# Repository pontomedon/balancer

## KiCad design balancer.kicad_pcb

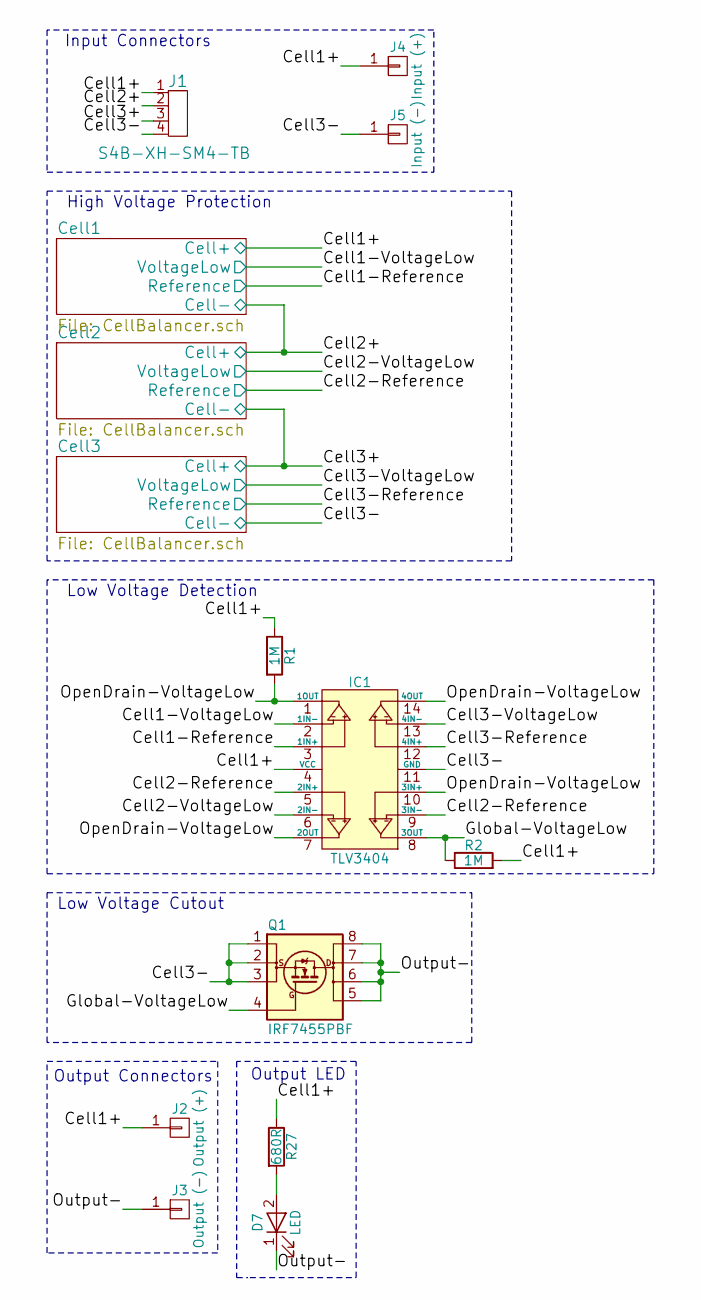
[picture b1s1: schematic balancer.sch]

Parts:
D7: LED; LED_0805
IC1: TLV3404; SOIC-14_3.9x8.7mm_Pitch1.27mm
J1: S4B-XH-SM4-TB; JST_XH_S4B-XH-SM4-TB_04x2.50mm_Angled
J2: Output (+); Solder_Terminal_4x4mm
J3: Output (-); Solder_Terminal_4x4mm
J4: Input (+); Solder_Terminal_4x4mm
J5: Input (-); Solder_Terminal_4x4mm
Q1: IRF7455PBF; SOIC-8_3.9x4.9mm_Pitch1.27mm
R1, R2: 1M; R_0805
R27: 680R; R_0805

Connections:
/Cell1+: IC1.4 (VCC), J1.1, J2.1, J4.1, R1.1, R2.2, R27.1; also elsewhere on the board
/Cell1-Reference: IC1.3 (1IN+); also elsewhere on the board
/Cell1-VoltageLow: IC1.2 (1IN-); also elsewhere on the board
/Cell2+: J1.2; also elsewhere on the board
/Cell2-Reference: IC1.5 (2IN+), IC1.9 (3IN-); also elsewhere on the board
/Cell2-VoltageLow: IC1.6 (2IN-); also elsewhere on the board
/Cell3+: J1.3; also elsewhere on the board
/Cell3-: IC1.11 (GND), J1.4, J5.1, Q1.1 (S), Q1.2 (S), Q1.3 (S); also elsewhere on the board
/Cell3-Reference: IC1.12 (4IN+); also elsewhere on the board
/Cell3-VoltageLow: IC1.13 (4IN-); also elsewhere on the board
/Global-VoltageLow: IC1.8 (3OUT), Q1.4 (G), R2.1
/OpenDrain-VoltageLow: IC1.1 (1OUT), IC1.7 (2OUT), IC1.10 (3IN+), IC1.14 (4OUT), R1.2
/Output-: D7.1 (K), J3.1, Q1.5 (D), Q1.6 (D), Q1.7 (D), Q1.8 (D)
unnamed: D7.2 (A), R27.2

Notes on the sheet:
Input Connectors
High Voltage Protection
Low Voltage Detection
Low Voltage Cutout
Output Connectors
Output LED

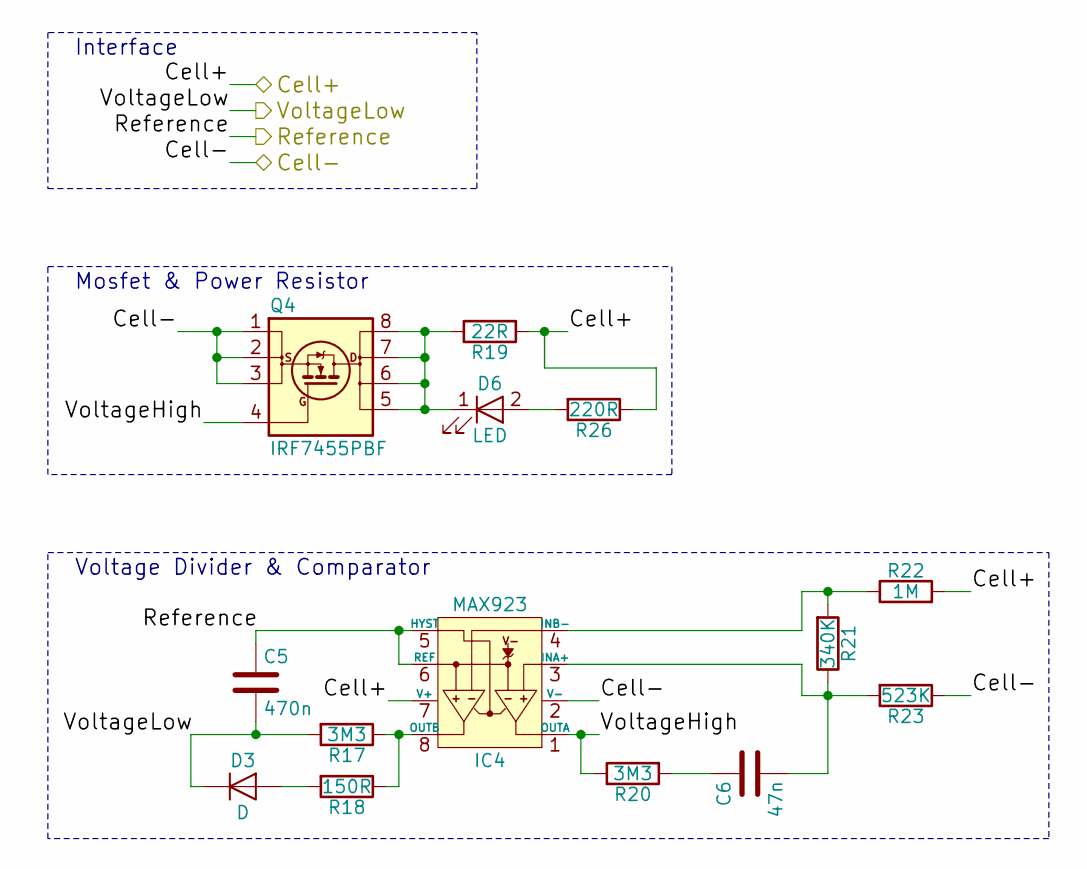
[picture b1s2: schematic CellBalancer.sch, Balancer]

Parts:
C1: 470n; C_0805
C2: 47n; C_0805
D1: D; D_0805
D4: LED; LED_0805
IC2: MAX923; SOIC-8_3.9x4.9mm_Pitch1.27mm
Q2: IRF7455PBF; SOIC-8_3.9x4.9mm_Pitch1.27mm
R3, R6: 3M3; R_0805
R4: 150R; R_0805
R5: 22R; R_0612
R7: 340K; R_0805
R8: 1M; R_0805
R9: 523K; R_0805
R24: 220R; R_0805

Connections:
/Cell1+: IC2.7 (V+), R5.2, R8.2, R24.1; also elsewhere on the board
/Cell1-Reference: C1.1, IC2.5 (HYST), IC2.6 (REF); also elsewhere on the board
/Cell1-VoltageLow: C1.2, D1.1 (K), R3.2; also elsewhere on the board
/Cell1/VoltageHigh: IC2.1 (OUTA), Q2.4 (G), R6.1
/Cell2+: IC2.2 (V-), Q2.1 (S), Q2.2 (S), Q2.3 (S), R9.1; also elsewhere on the board
unnamed: C2.1, R6.2
unnamed: C2.2, IC2.3 (INA+), R7.1, R9.2
unnamed: D1.2 (A), R4.2
unnamed: D4.1 (K), Q2.5 (D), Q2.6 (D), Q2.7 (D), Q2.8 (D), R5.1
unnamed: D4.2 (A), R24.2
unnamed: IC2.4 (INB-), R7.2, R8.1
unnamed: IC2.8 (OUTB), R3.1, R4.1

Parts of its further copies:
C3, C5: 470n; C_0805
C4, C6: 47n; C_0805
D2, D3: D; D_0805
D5, D6: LED; LED_0805
IC3, IC4: MAX923; SOIC-8_3.9x4.9mm_Pitch1.27mm
Q3, Q4: IRF7455PBF; SOIC-8_3.9x4.9mm_Pitch1.27mm
R10, R13, R17, R20: 3M3; R_0805
R11, R18: 150R; R_0805
R12, R19: 22R; R_0612
R14, R21: 340K; R_0805
R15, R22: 1M; R_0805
R16, R23: 523K; R_0805
R25, R26: 220R; R_0805

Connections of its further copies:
/Cell2+: IC3.7 (V+), R12.2, R15.2, R25.1; also elsewhere on the board
/Cell2-Reference: C3.1, IC3.5 (HYST), IC3.6 (REF); also elsewhere on the board
/Cell2-VoltageLow: C3.2, D2.1 (K), R10.2; also elsewhere on the board
/Cell2/VoltageHigh: IC3.1 (OUTA), Q3.4 (G), R13.1
/Cell3+: IC3.2 (V-), IC4.7 (V+), Q3.1 (S), Q3.2 (S), Q3.3 (S), R16.1, R19.2, R22.2, R26.1; also elsewhere on the board
/Cell3-: IC4.2 (V-), Q4.1 (S), Q4.2 (S), Q4.3 (S), R23.1; also elsewhere on the board
/Cell3-Reference: C5.1, IC4.5 (HYST), IC4.6 (REF); also elsewhere on the board
/Cell3-VoltageLow: C5.2, D3.1 (K), R17.2; also elsewhere on the board
/Cell3/VoltageHigh: IC4.1 (OUTA), Q4.4 (G), R20.1
unnamed: C4.1, R13.2
unnamed: C4.2, IC3.3 (INA+), R14.1, R16.2
unnamed: C6.1, R20.2
unnamed: C6.2, IC4.3 (INA+), R21.1, R23.2
unnamed: D2.2 (A), R11.2
unnamed: D3.2 (A), R18.2
unnamed: D5.1 (K), Q3.5 (D), Q3.6 (D), Q3.7 (D), Q3.8 (D), R12.1
unnamed: D5.2 (A), R25.2
unnamed: D6.1 (K), Q4.5 (D), Q4.6 (D), Q4.7 (D), Q4.8 (D), R19.1
unnamed: D6.2 (A), R26.2
unnamed: IC3.4 (INB-), R14.2, R15.1
unnamed: IC3.8 (OUTB), R10.1, R11.1
unnamed: IC4.4 (INB-), R21.2, R22.1
unnamed: IC4.8 (OUTB), R17.1, R18.1

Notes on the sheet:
Interface
Mosfet & Power Resistor
Voltage Divider & Comparator

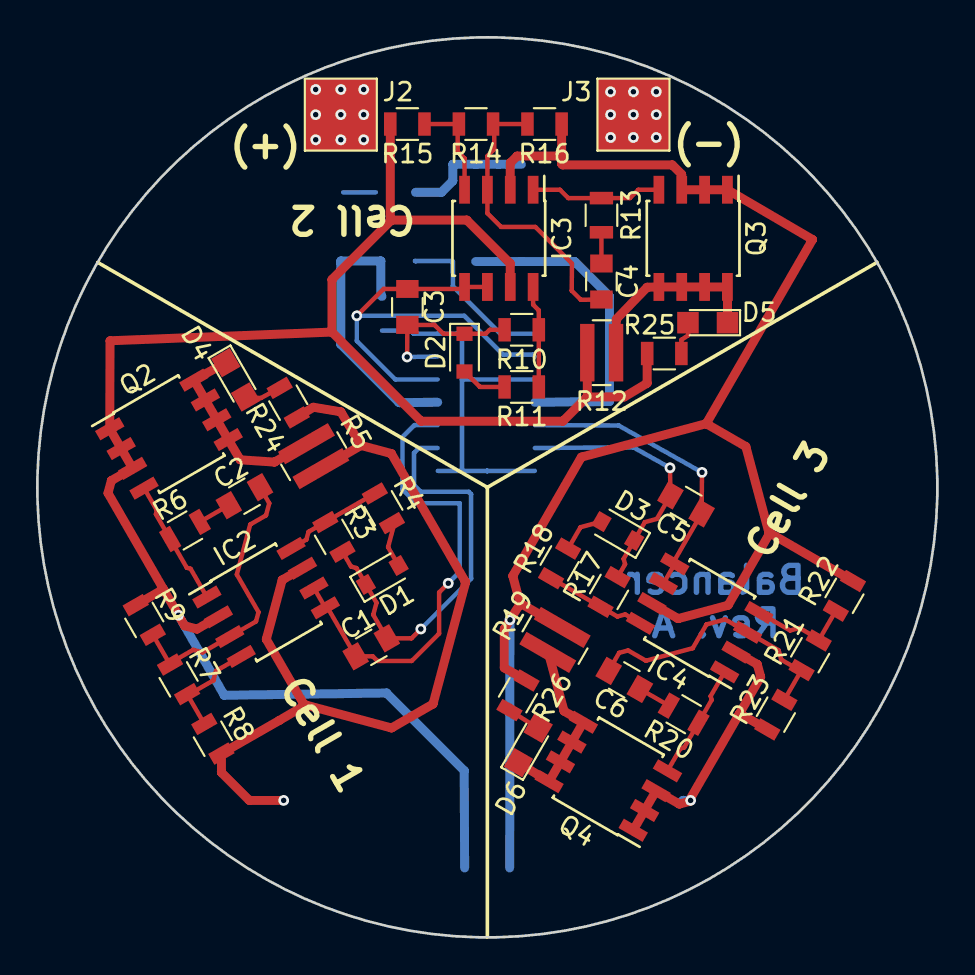
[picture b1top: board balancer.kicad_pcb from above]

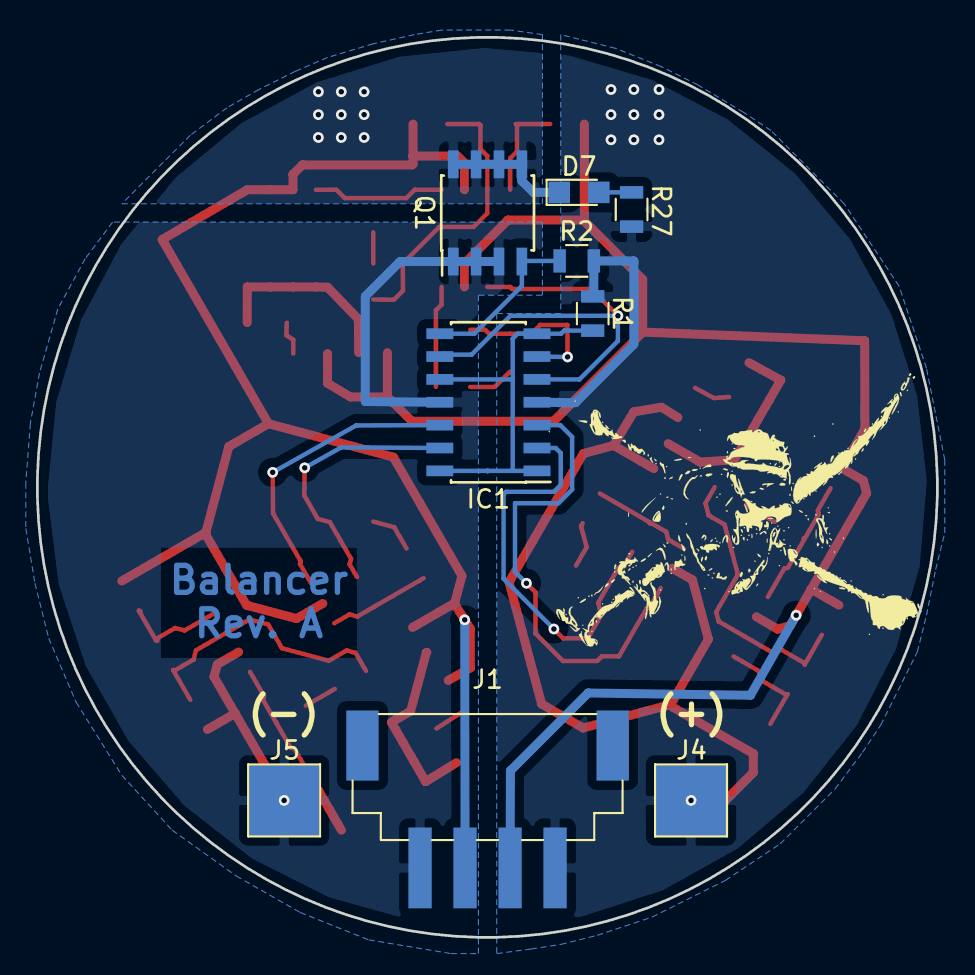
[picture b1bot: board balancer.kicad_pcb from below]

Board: 2 copper layers, 50.0 x 50.0 mm, 53 parts (9 on the bottom side), 38 nets.

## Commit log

2017-03-17 initial commit, added readme
2017-03-18 added project file, component library and schematic added empty pcb
2017-03-18 added 3d models for the XH connector
2017-03-18 added SOIC-8 footprint
2017-03-18 added the XH connector footprint into the footprint lib
2017-03-18 added tlv3404
2017-03-18 added a CellBalancer sheet
2017-03-18 added hierarchical sheets and an xh connector
2017-03-18 high voltage protection done
2017-03-18 schematic done
2017-03-18 added annotations
2017-03-18 changed burner resistor to 22R, assigned all footprints
2017-03-18 Front side pcb first version
2017-03-19 layout finalized
2017-03-19 generated gerbers
2017-03-19 added missing gerbers
2017-03-19 added missing 3d models, recreated gerbers and drill files
2017-03-19 update silkscreen
2017-03-19 added netlist and bom
2017-03-20 added copper text on bottom, logo on bottom silkscreen
2017-03-20 final version sent off to board manufacturer
2017-03-20 added zip file that was sent to leiton
2017-03-20 deleted ps version of drl map
2017-03-20 added rev_a1 zip
2017-05-07 changed the pull-ups on the TLV to 1M
2017-06-12 updated pull ups on quad comparator to 1M, update center divider resistor to 340K to be closer to 4.2V charge cutoff
